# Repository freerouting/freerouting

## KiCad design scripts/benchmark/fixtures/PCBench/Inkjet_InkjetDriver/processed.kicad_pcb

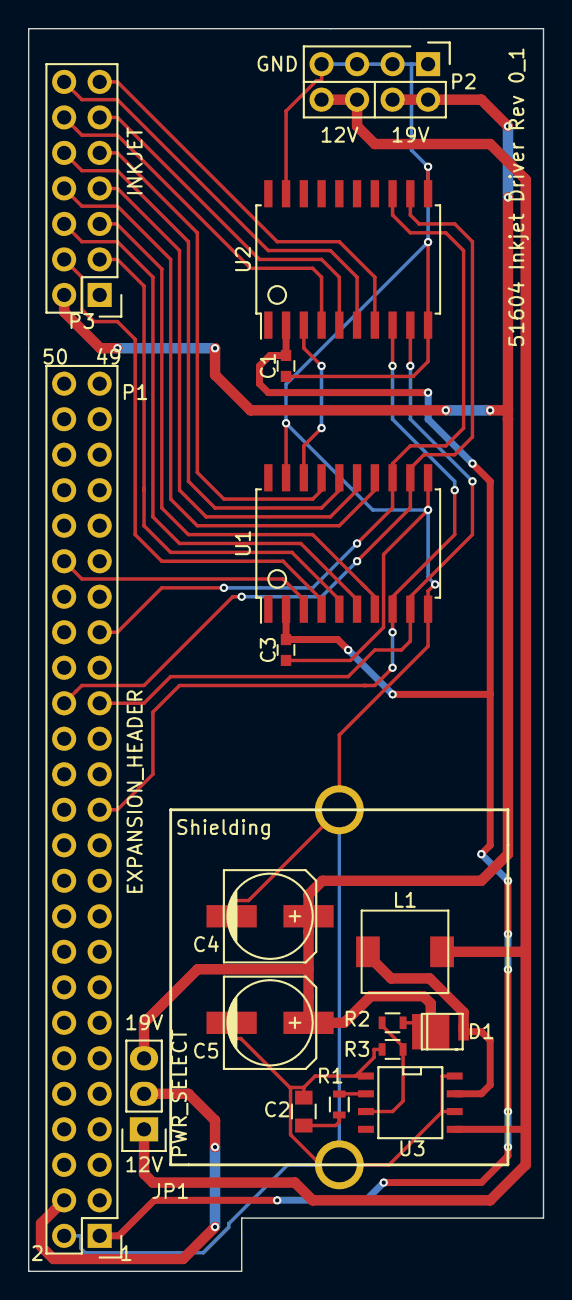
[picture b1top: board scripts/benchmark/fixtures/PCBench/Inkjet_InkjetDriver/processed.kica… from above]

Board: 2 copper layers, 36.8 x 88.9 mm, 19 parts (0 on the bottom side), 27 nets.

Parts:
C1, C3: 0.1uF; C_0603
C2: 1uF; C_0805
C4, C5: 100uF; c_elec_6.3x7.7
D1: SS3P4; DO-220_Diode
JP1: PWR_SELECT; Socket_Strip_Straight_1x03
L1: 220uH; CLF6045_Inductor
P1: EXPANSION_HEADER; Pin_Header_Straight_2x25
P2: PWR; Pin_Header_Straight_2x04_Silk_Change
P3: INKJET; Pin_Header_Straight_2x07
R1: 1k; R_0603
R2: 18.7k; R_0603
R3: 1.27k; R_0603
SM1: Shielding; SolderWirePad_single_2-5mmDrill
SM2: Shield; SolderWirePad_single_2-5mmDrill
U1, U2: 6B595; SOIC-20_7.5x12.8mm_Pitch1.27mm
U3: LT1072; SOIC-8-N

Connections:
19V: C4.1, C5.1, D1.1, JP1.3, P2.2, P2.4, P3.2, R2.1
+5V: C1.1, C3.1, P1.1, U1.2, U2.2
+12V: JP1.1, L1.1, P2.6, P2.8, U3.5
GND: C1.2, C2.2, C3.2, C4.2, C5.2, P1.2, P2.1, P2.3, P2.5, P2.7, R3.2, SM1.1, SM2.1, U1.10, U1.11, U1.19, U2.10, U2.11, U2.19, U3.1, U3.6, U3.8
unnamed: C2.1, R1.2
unnamed: D1.2, L1.2, U3.7
unnamed: JP1.2, P1.4
unnamed: P1.25, U1.8, U2.8
unnamed: P1.31, U1.9, U2.9
unnamed: P1.32, U1.12, U2.12
unnamed: P1.35, U1.13, U2.13
unnamed: P1.40, U1.3
unnamed: P3.3, U1.5
unnamed: P3.4, U1.4
unnamed: P3.5, U1.7
unnamed: P3.6, U1.6
unnamed: P3.7, U1.15
unnamed: P3.8, U1.14
unnamed: P3.9, U1.17
unnamed: P3.10, U1.16
unnamed: P3.11, U2.5
unnamed: P3.12, U2.4
unnamed: P3.13, U2.7
unnamed: P3.14, U2.6
unnamed: R1.1, U3.2
unnamed: R2.2, R3.1, U3.3
unnamed: U1.18, U2.3

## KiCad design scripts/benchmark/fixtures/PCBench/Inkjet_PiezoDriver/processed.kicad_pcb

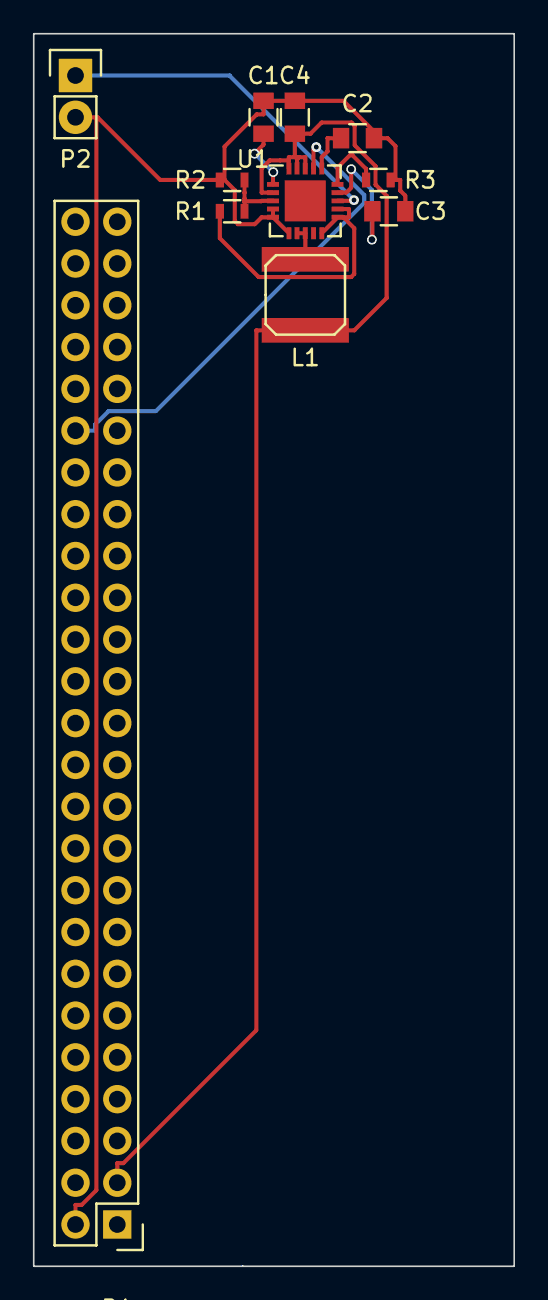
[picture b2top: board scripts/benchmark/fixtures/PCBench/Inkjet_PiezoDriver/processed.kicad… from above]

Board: 2 copper layers, 29.2 x 74.9 mm, 11 parts (0 on the bottom side), 11 nets.

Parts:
C1, C2, C3, C4: C; C_0805
L1: INDUCTOR; SELF-WE-TPC_M
P1: CONN_02X25; Pin_Header_Straight_2x25
P2: CONN_01X02; Pin_Header_Straight_1x02
R1, R2, R3: R; R_0603
U1: DRV8662; QFN-20-1EP_4x4mm_Pitch0.5mm

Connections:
GND: C1.2, C2.2, C3.2, C4.2, P1.2, P2.2, R2.2, R3.1, U1.4, U1.5, U1.6
unnamed: C1.1, U1.1
unnamed: C2.1, U1.16
unnamed: C3.1, U1.14
unnamed: L1.2, U1.7, U1.8
unnamed: P1.40, U1.17
unnamed: P2.1, U1.13
unnamed: R1.1, U1.10, U1.11, U1.12
unnamed: R1.2, R2.1, U1.3
unnamed: R3.2, U1.15
VDD: C4.1, L1.1, P1.3, U1.2, U1.18, U1.19, U1.20
